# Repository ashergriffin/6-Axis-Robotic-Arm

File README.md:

# 6-Axis-Robotic-Arm
Creating an almost fully custom 6-axis robotic arm

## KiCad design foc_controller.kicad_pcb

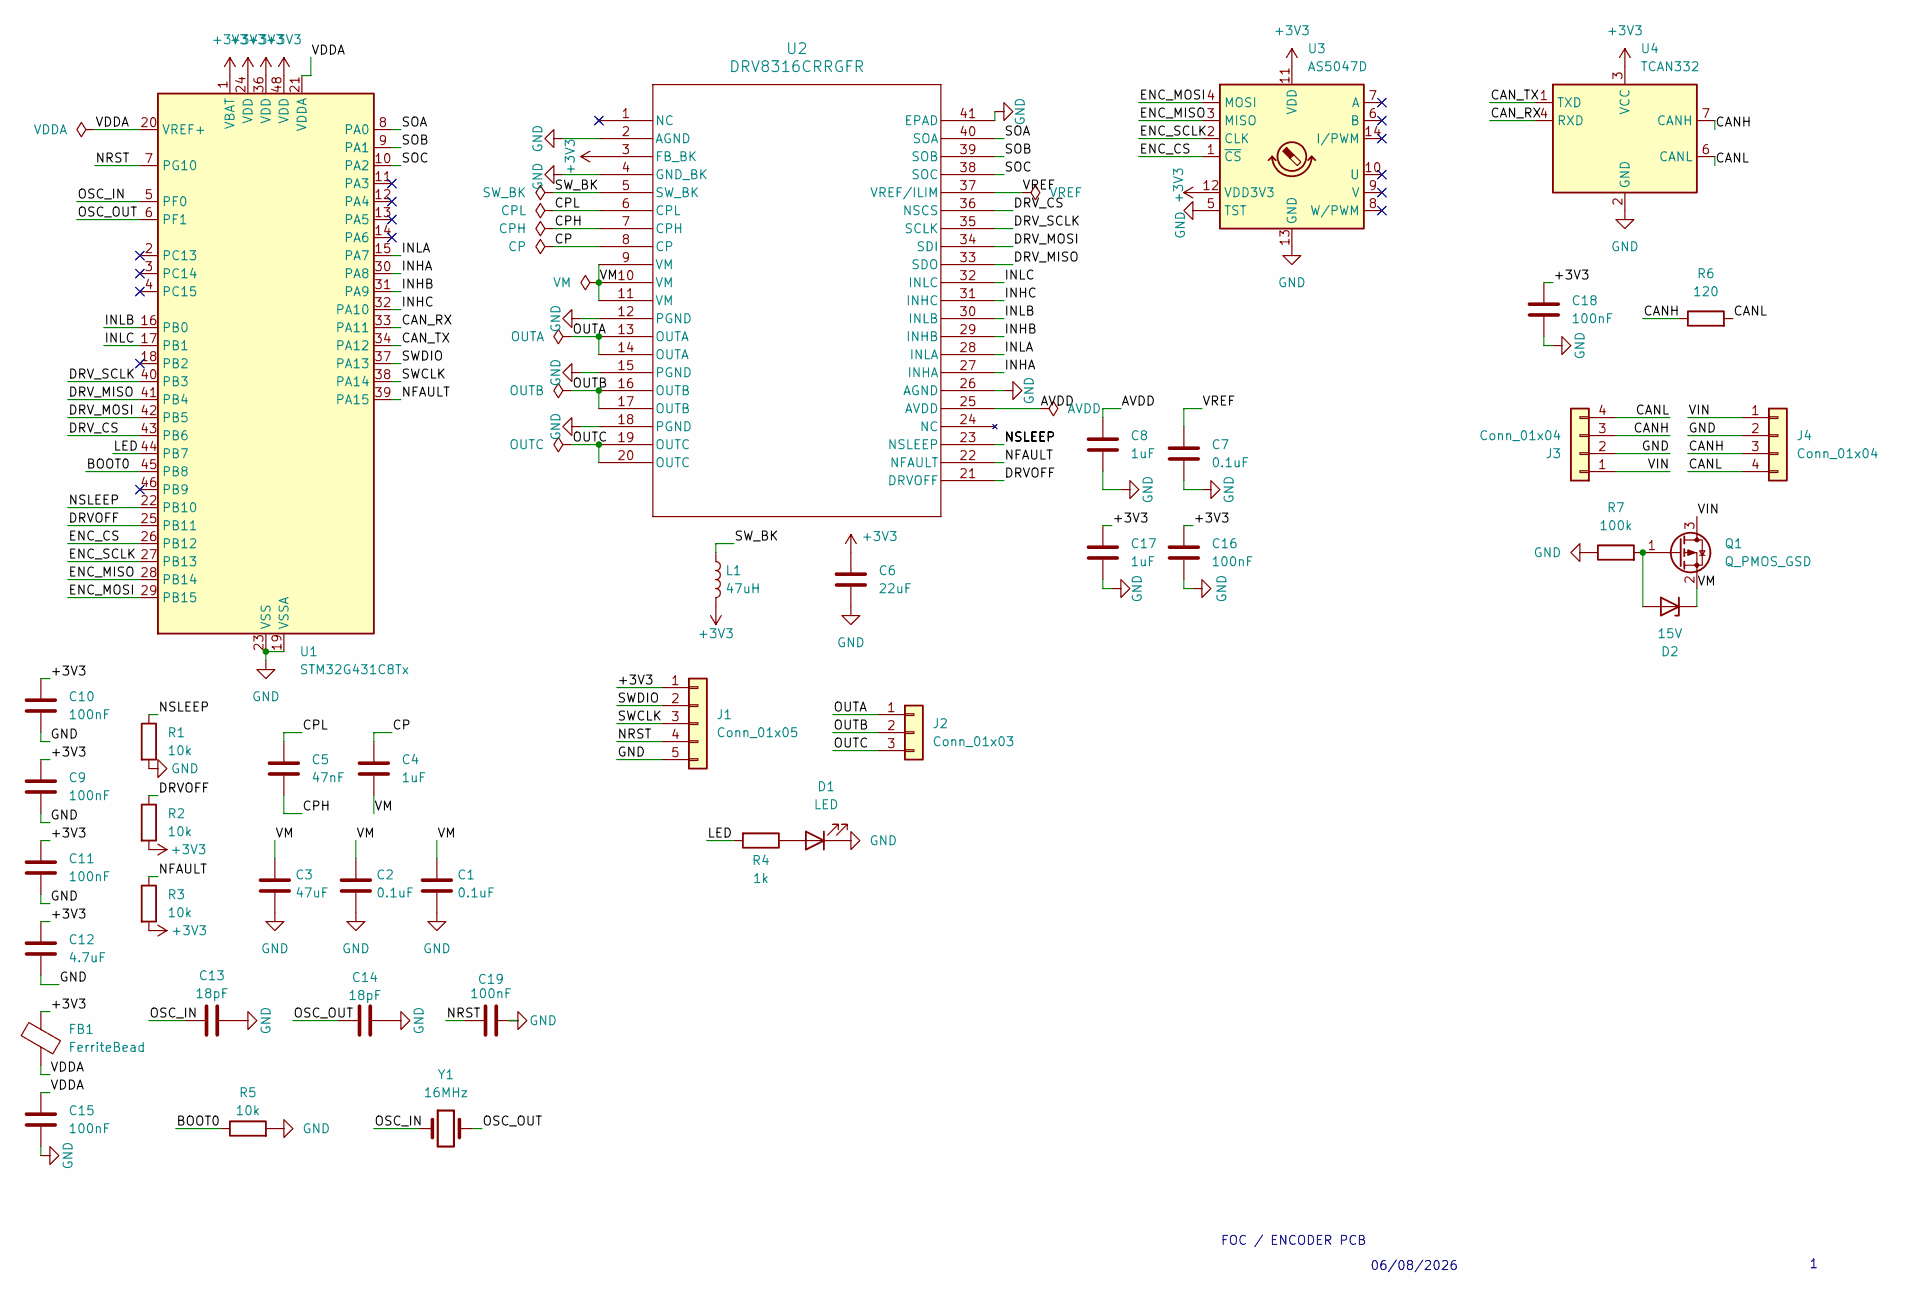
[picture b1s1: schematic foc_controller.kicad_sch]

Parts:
C1, C2, C7: 0.1uF; C_0603_1608Metric
C3: 47uF; CP_Elec_6.3x7.7
C4, C8, C17: 1uF; C_0603_1608Metric
C5: 47nF; C_0603_1608Metric
C6: 22uF; C_0805_2012Metric
C9, C10, C11, C15, C16, C18, C19: 100nF; C_0603_1608Metric
C12: 4.7uF; C_0805_2012Metric
C13, C14: 18pF; C_0603_1608Metric
D1: LED; LED_0603_1608Metric
D2: 15V; D_SOD-123
FB1: FerriteBead; L_0603_1608Metric
J1: Conn_01x05; JST_VH_S5P-VH_1x05_P3.96mm_Horizontal
J2: Conn_01x03; JST_VH_S3P-VH_1x03_P3.96mm_Horizontal
J3, J4: Conn_01x04; JST_VH_S4P-VH_1x04_P3.96mm_Horizontal
L1: 47uH; L_Sunlord_SWPA4030S
Q1: Q_PMOS_GSD; SOT-23
R1, R2, R3, R5: 10k; R_0603_1608Metric
R4: 1k; R_0603_1608Metric
R6: 120; R_0603_1608Metric
R7: 100k; R_0603_1608Metric
U1: STM32G431C8Tx; LQFP-48_7x7mm_P0.5mm
U2: DRV8316CRRGFR; VQFN40_RGF_TEX
U3: AS5047D; TSSOP-14_4.4x5mm_P0.65mm
U4: TCAN332; SOIC-8_3.9x4.9mm_P1.27mm
Y1: 16MHz; Crystal_SMD_3215-2Pin_3.2x1.5mm

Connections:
+3V3: C6.1, C9.1, C10.1, C11.1, C12.1, C16.1, C17.1, C18.1, FB1.1, J1.1, L1.2, R2.2, R3.2, U1.1 (VBAT), U1.24 (VDD), U1.36 (VDD), U1.48 (VDD), U2.3 (FB_BK), U3.11 (VDD), U3.12 (VDD3V3), U4.3 (VCC)
/AVDD: C8.1, U2.25 (AVDD)
/BOOT0: R5.1, U1.45 (PB8)
/CANH: J3.3, J4.3, R6.1, U4.7 (CANH)
/CANL: J3.4, J4.4, R6.2, U4.6 (CANL)
/CAN_RX: U1.33 (PA11), U4.4 (RXD)
/CAN_TX: U1.34 (PA12), U4.1 (TXD)
/CP: C4.1, U2.8 (CP)
/CPH: C5.2, U2.7 (CPH)
/CPL: C5.1, U2.6 (CPL)
/DRVOFF: R2.1, U1.25 (PB11), U2.21 (DRVOFF)
/DRV_CS: U1.43 (PB6), U2.36 (NSCS)
/DRV_MISO: U1.41 (PB4), U2.33 (SDO)
/DRV_MOSI: U1.42 (PB5), U2.34 (SDI)
/DRV_SCLK: U1.40 (PB3), U2.35 (SCLK)
/ENC_CS: U1.26 (PB12), U3.1 (~CS)
/ENC_MISO: U1.28 (PB14), U3.3 (MISO)
/ENC_MOSI: U1.29 (PB15), U3.4 (MOSI)
/ENC_SCLK: U1.27 (PB13), U3.2 (CLK)
/INHA: U1.30 (PA8), U2.27 (INHA)
/INHB: U1.31 (PA9), U2.29 (INHB)
/INHC: U1.32 (PA10), U2.31 (INHC)
/INLA: U1.15 (PA7), U2.28 (INLA)
/INLB: U1.16 (PB0), U2.30 (INLB)
/INLC: U1.17 (PB1), U2.32 (INLC)
/LED: R4.2, U1.44 (PB7)
/NFAULT: R3.1, U1.39 (PA15), U2.22 (NFAULT)
/NRST: C19.2, J1.4, U1.7 (PG10)
/NSLEEP: R1.1, U1.22 (PB10), U2.23 (NSLEEP)
/OSC_IN: C13.2, U1.5 (PF0), Y1.1
/OSC_OUT: C14.1, U1.6 (PF1), Y1.2
/OUTA: J2.1, U2.13 (OUTA), U2.14 (OUTA)
/OUTB: J2.2, U2.16 (OUTB), U2.17 (OUTB)
/OUTC: J2.3, U2.19 (OUTC), U2.20 (OUTC)
/SOA: U1.8 (PA0), U2.40 (SOA)
/SOB: U1.9 (PA1), U2.39 (SOB)
/SOC: U1.10 (PA2), U2.38 (SOC)
/SWCLK: J1.3, U1.38 (PA14)
/SWDIO: J1.2, U1.37 (PA13)
/SW_BK: L1.1, U2.5 (SW_BK)
/VDDA: C15.1, FB1.2, U1.20 (VREF+), U1.21 (VDDA)
/VIN: J3.1, J4.1, Q1.3 (D)
/VM: C1.1, C2.1, C3.1, C4.2, D2.1 (K), Q1.2 (S), U2.9 (VM), U2.10 (VM), U2.11 (VM)
/VREF: C7.1, U2.37 (VREF/ILIM)
GND: C1.2, C2.2, C3.2, C6.2, C7.2, C8.2, C9.2, C10.2, C11.2, C12.2, C13.1, C14.2, C15.2, C16.2, C17.2, C18.2, C19.1, D1.1 (K), J1.5, J3.2, J4.2, R1.2, R5.2, R7.1, U1.19 (VSSA), U1.23 (VSS), U1.35 (VSS), U1.47 (VSS), U2.2 (AGND), U2.4 (GND_BK), U2.12 (PGND), U2.15 (PGND), U2.18 (PGND), U2.26 (AGND), U2.41 (EPAD), U3.5 (TST), U3.13 (GND), U4.2 (GND)
unnamed: D1.2 (A), R4.1
unnamed: D2.2 (A), Q1.1 (G), R7.2

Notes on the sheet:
06/08/2026
FOC / ENCODER PCB

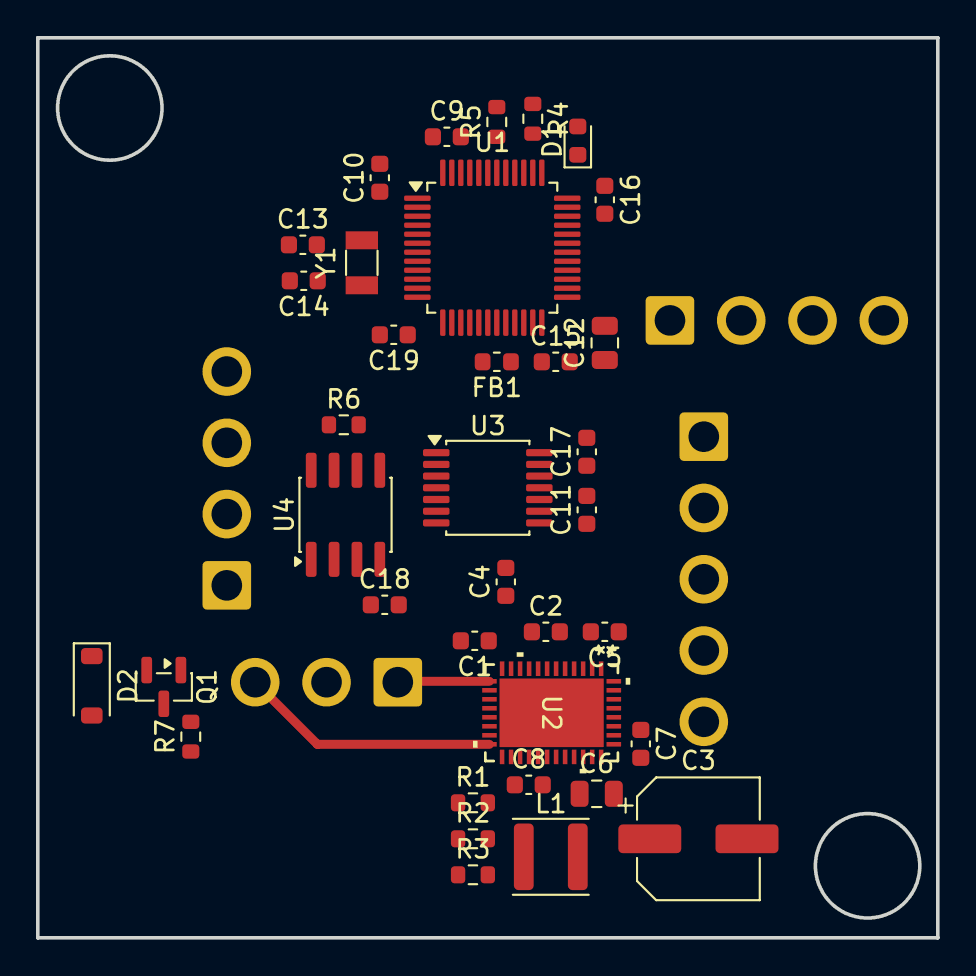
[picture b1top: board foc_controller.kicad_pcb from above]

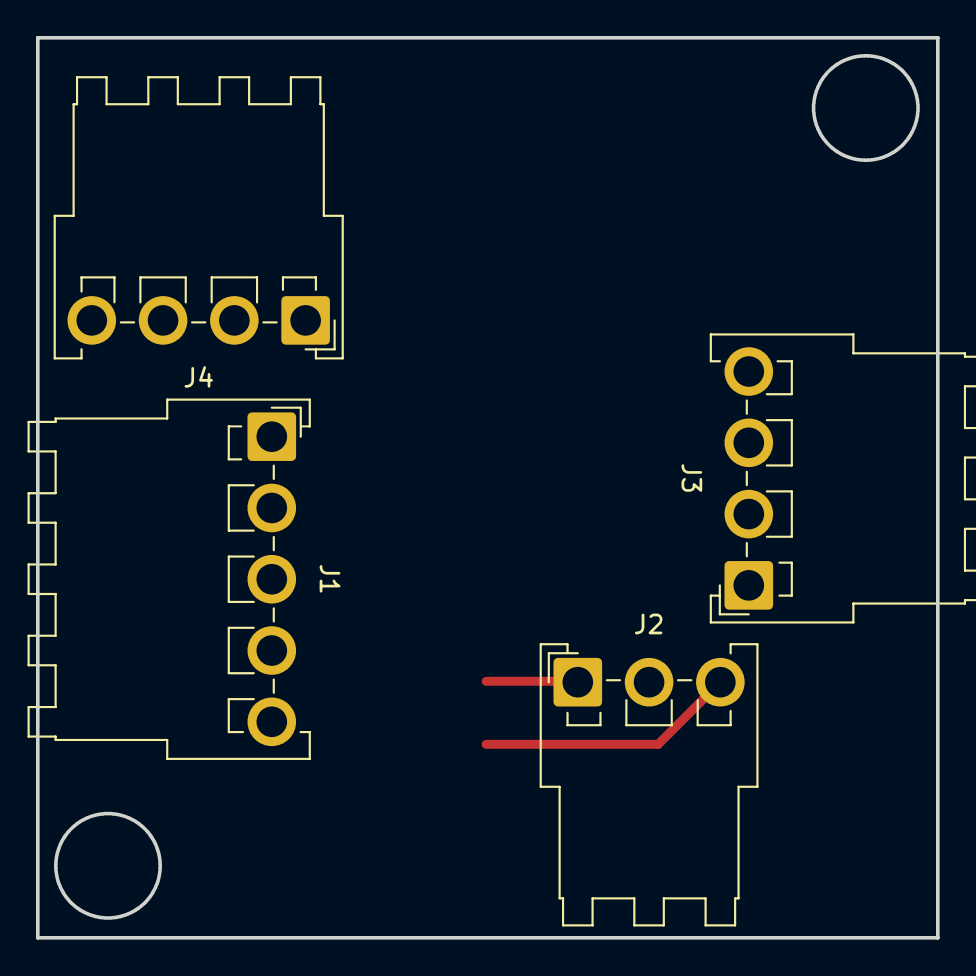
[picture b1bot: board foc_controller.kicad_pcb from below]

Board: 4 copper layers, 50.0 x 50.0 mm, 40 parts (4 on the bottom side), 47 nets.
